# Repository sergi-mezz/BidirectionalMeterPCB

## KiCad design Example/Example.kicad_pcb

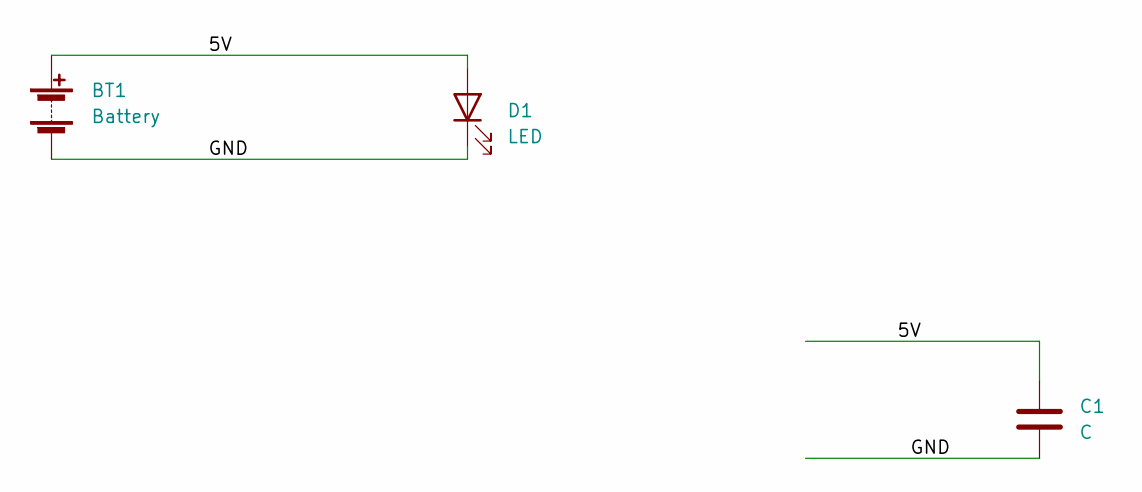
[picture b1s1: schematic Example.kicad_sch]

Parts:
BT1: Battery; Battery_Panasonic_CR1025-VSK_Vertical_CircularHoles
C1: C; C_0201_0603Metric_Pad0.64x0.40mm_HandSolder
D1: LED; LED_0201_0603Metric_Pad0.64x0.40mm_HandSolder

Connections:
/5V: BT1.1 (+), C1.1, D1.2 (A)
/GND: BT1.2 (-), C1.2, D1.1 (K)

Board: 2 copper layers, 3 parts (0 on the bottom side), 2 nets, no tracks yet.

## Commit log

2023-05-19 se añade resistencia para pickit
2023-05-23 se actualiza circuito de conector de pickit
2023-05-24 se quita conecxion de pin rst en rn4870 y se agrega conector para jumper en mclr de pic
2023-05-27 correcion de diagrama
